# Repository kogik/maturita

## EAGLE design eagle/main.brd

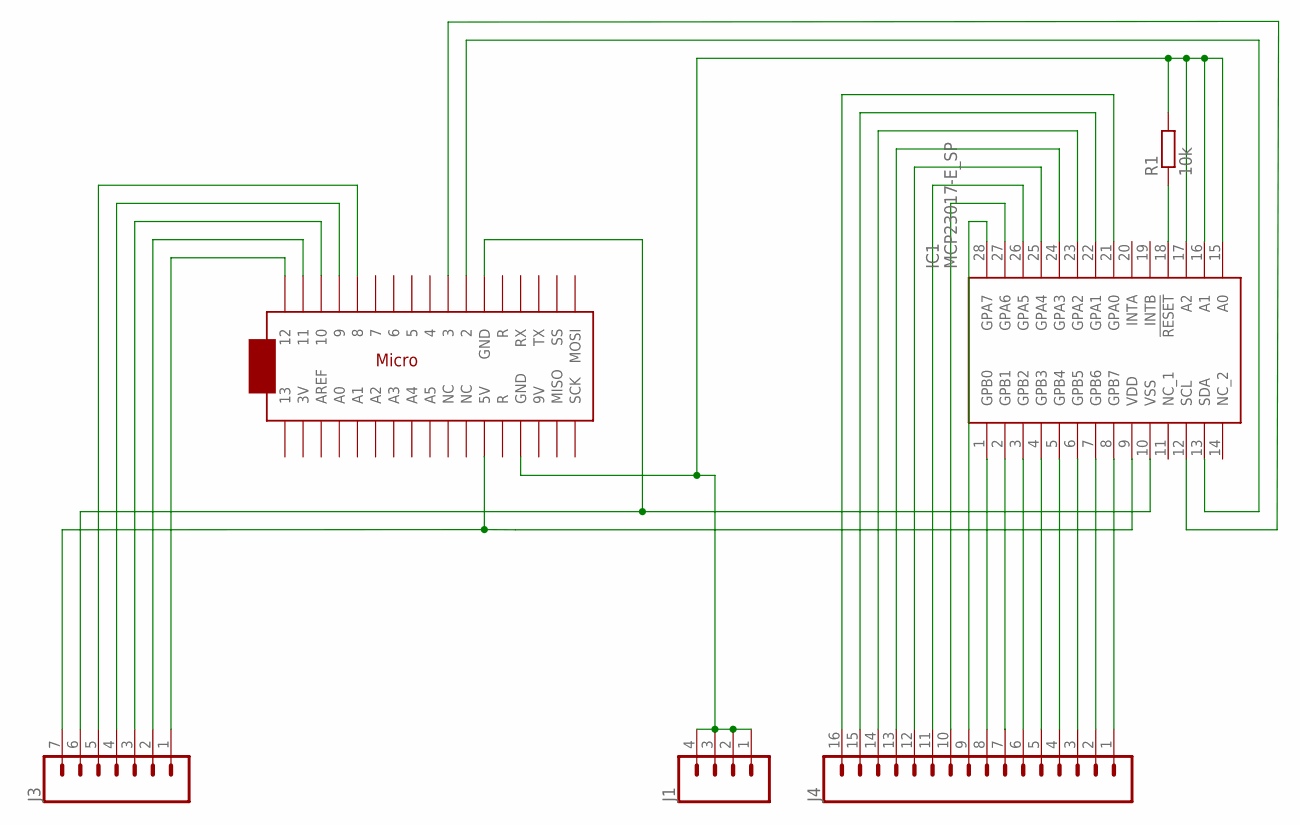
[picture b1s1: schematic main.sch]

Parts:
IC1: MCP23017-E_SP; DIP794W56P254L3486H508Q28N
J1: CONN_04PTH; 1X04
J3: CONN_07; 1X07
J4: CONN_16; 1X16
R1: 10k; 0207/10
U$1: ARDUINOMICRO

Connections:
unnamed: IC1.18 (!RESET), R1.1
unnamed: IC1.9 (VDD), J3.7, U$1.P$23 (5V)
unnamed: J3.3, U$1.P$3 (10)
unnamed: IC1.13 (SDA), U$1.P$11 (2)
unnamed: IC1.12 (SCL), U$1.P$10 (3)
unnamed: IC1.15 (A0), IC1.16 (A1), IC1.17 (A2), J1.1, J1.2, J1.3, J1.4, R1.2, U$1.P$12 (GND)
unnamed: IC1.8 (GPB7), J4.1
unnamed: IC1.7 (GPB6), J4.2
unnamed: IC1.6 (GPB5), J4.3
unnamed: IC1.5 (GPB4), J4.4
unnamed: IC1.4 (GPB3), J4.5
unnamed: IC1.2 (GPB1), J4.7
unnamed: IC1.3 (GPB2), J4.6
unnamed: IC1.1 (GPB0), J4.8
unnamed: IC1.21 (GPA0), J4.16
unnamed: IC1.22 (GPA1), J4.15
unnamed: IC1.23 (GPA2), J4.14
unnamed: IC1.24 (GPA3), J4.13
unnamed: IC1.25 (GPA4), J4.12
unnamed: IC1.26 (GPA5), J4.11
unnamed: IC1.27 (GPA6), J4.10
unnamed: IC1.28 (GPA7), J4.9
unnamed: IC1.10 (VSS), J3.6, U$1.P$21 (GND)
unnamed: J3.2, U$1.P$2 (11)
unnamed: J3.4, U$1.P$4 (9)
unnamed: J3.5, U$1.P$5 (8)
unnamed: J3.1, U$1.P$1 (12)

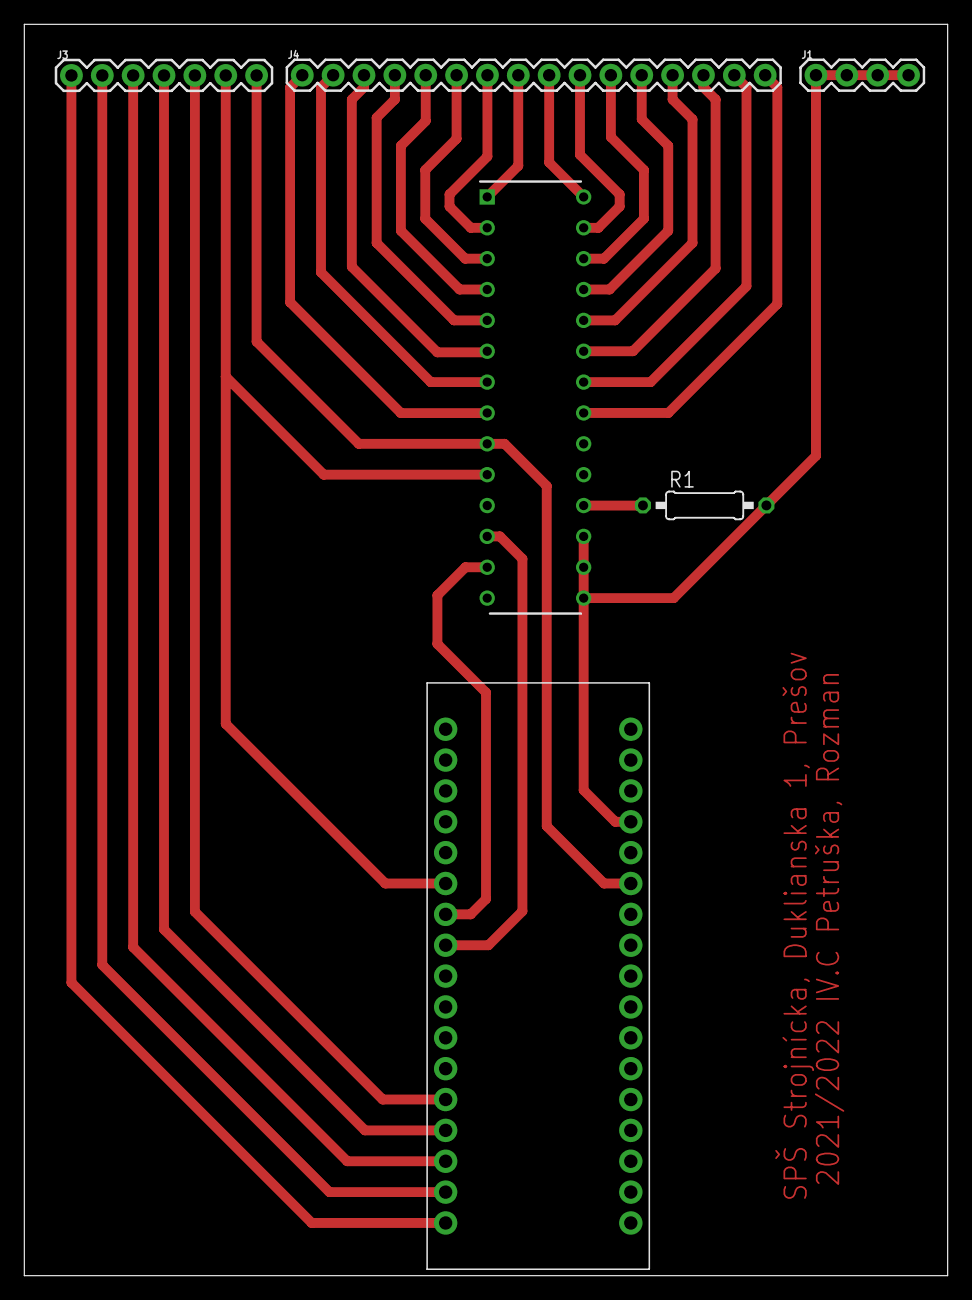
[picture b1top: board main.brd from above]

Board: 2 copper layers, 76.0 x 103.0 mm, 6 parts (0 on the bottom side), 27 nets.

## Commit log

2022-03-06 eagle
2022-03-08 eagle parts
2022-03-21 desktopApp v2

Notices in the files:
parts and their libraries:
SparkFun-Connectors: Licensing: Creative Commons ShareAlike 4.0 International - https://creativecommons.org/licenses/by-sa/4.0
